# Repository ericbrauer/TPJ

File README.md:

# TPJ
Final Project for ECT @ Seneca. "Project Skylight"

# PROJECT SKYLIGHT
Eric Brauer 

## Executive Summary
Project Skylight is an Internet-connected light that simulates daylight cycles. It’s meant for
use in places where there are no external windows, and it can be used to get a quick visual
reference for the time of day. Project skylight is composed of a small microcontroller with wifi
capabilities, and 16 RGB LEDs. The device is meant to run with very little set-up, but a
web-based user interface can be used for further configuration. In the report, the operation
and specifications of Project Skylight are covered in more detail.

## Functional Features
The product requirements, as envisioned, are as follows:
- Project Skylight (PS) asks for WiFi credentials, and connects to a WiFi router.
- PS serves a webpage which is used to configure the device and to provide the user’s
city of residence.
- PS uses the OpenWeatherMap API to get the time of dawn and dusk. The device
also uses an NTP server to synchronise the current time.
- PS changes the colour and brightness of LEDs based on current time in reference to
sunrise and sunset times.
- PS monitors a potentiometer, which will be used to dim or turn off the LED light.
- Further configuration is possible from the web interface. This includes setting manual
daylight times.

## Product Specifications
- Powered from micro USB port
- Operates at nominal indoor temperatures, not for outdoor use
- Luminosity of around 200 - 400 Lumens
- WiFi range 20m
- Current consumption no higher than 1.5A

## Theory of Operation
### Power Concerns
The ESP-12f requires a typical voltage of 3.3 Volts. The Neopixel array require a voltage of 4
to 7 Volts. Thus a voltage regulation stage is required. USB provides 5 Volts, and this power
is used for the Neopixels. Power for the ESP-12f is supplied by an LD1117.

Power consumption is based heavily on several factors: transmission and reception by the
WiFi module on the ESP-12f, signal strength of the same, and brightness levels of the
Neopixels. If a single Neopixel is set to white with maximum brightness, then each of its
three RGB LEDs requires 20 mA. There is never a situation when the Skylight is generating
this state, however. Full brightness of the daytime SkyState would represent the maximum
current consumption.

4 LEDs displaying white = 60mA * 4 240mA

12 LEDs displaying cyan = 40mA * 12 480mA

Total Current for Neopixels: **720mA**

In addition, the ESP-12f requires a maximum of 100mA. Meaning that a USB adapter rated
at 1A should be sufficient for proper function and also provide a buffer of almost 20%.

### Initial State / Connectivity
The ESP-12f is a popular IC among the maker community, and much work has been done to
implement a thorough Arduino library which exposes much of the connectivity capability of
the chip. The Skylight in particular makes use of several libraries to implement the initial
Access Point state (used to enter WiFi credentials), to communicate to OpenWeatherMap,
and to serve a web-based user interface.

**ESP8266WiFi** exposes functions for connecting to a WiFi access point and communicating
over TCP/IP.

**ESP8266WebServer** allows to ESP to also act as a web server, and serve HTTP code to
clients.

**ESP8266mDNS** provides a ‘micro DNS’ server which will associate a URL with whatever IP
address is assigned to the ESP’s web server.

**WifiManager** checks flash for a WiFi SSID and password that was previously used to
connect. If these don’t exist, WifiManager will set the ESP-12 to station mode with an SSID
set in software. The user can connect to this access point, and then navigate to the url
specified by the micro-DNS server. From this webpage, the user has the option to scan for
available access points, and then enter a password to connect to this access point. From
this point, the ESP exits station mode and attempts to connect to the access point as a
client. If it is successful, these credentials will be saved in flash memory to be used on
startup.

### The Web Interface
The ESP handles web requests directed at the url created by the micro DNS server. On the
Skylight, the url is skylight.local. The main interface is located at the root. Other webpages
are used to acknowledge user requests, and exist at /submit, /demo and /reset. All other
requests will result in a HTTP code of 404.
A typical user request is to manually change the time at which a sunset event occurs. The
time desired is typed into text boxes, and the ‘save’ button is pressed. Information inside the
text boxes is saved as arguments. The arguments are validated first. The arguments are
checked to ensure that they are numerical and in a proper 12-hour time format. A bad
request will result in a ‘bad request’ message and a link back to the root page. A good
request will be accepted. Finally, the browser will navigate to skylight.local/submit, where the
user is notified that the alarm has been set.

### Adafruit NeoPixel Array
Neopixels are addressable RGB LEDs. Control circuitry, LEDs, and internal oscillators are all
included in one package. Data can be received from a microcontroller at speeds of 800kbps,
and outputted to the next neopixel. This allows an array of neopixels to be controlled from
one data pin.
Each neopixel requires 24bits of information. The first neopixel uses 24 bits to set the values
of discrete red, green and blue LEDs. Each of these LEDs takes a PWM 8-bit signal to set its
intensity, resulting in 255 possible states. Once the state of neopixel has been set,
subsequent data is amplified and sent through a ‘Data Out’ line to program the next
neopixel. The advantage of neopixels is their flexibility, but larger arrays will require far more
memory and processing than some microcontrollers can provide. Since the Skylight uses
only 16 neopixels, performance requirements are relatively light.9
Adafruit provides an Arduino Library for communicating with the Neopixel array. The
Neopixels are powered from a 5V VCC line and the data line is connected to the ESP’s
GPIO pin 14.
### Brightness Control
A potentiometer is connected to the ESP-12’s single Analog-to-Digital converter. A standard
Arduino library function is used to convert this number to a 10-bit value, which is then to an
8-bit value using bit shift. The 8-bit value is used as an argument for the setBrightness
function which is part of the Adafruit Neopixel library. Using the ADC with interrupts proved
to be problematic, and so the ADC is polled in loop() and if its value changes, the
setBrightness function is called. The potentiometer is connected to the ADC pin identified as
0.
### Setting dusk_time and dawn_time From OpenWeatherMap.org
OpenWeatherMap provides an API that can be used for free with registration for a smaller
number of requests. For the Skylight prototype, this is sufficient. Documentation for the API
is located at ​ [OpenWeatherMap](http://openweathermap.org/current).​ The API can be used with several different
formats of location data; for simplicity’s sake a GET request is used encoded with the city
and country code are used along with an API key.
The HTTP response is in a JSON format. First, the HTTP header of the response is
discarded. Then ArduinoJson library is used to parse the response. Most information is
related to weather conditions and is not used. The sunrise and sunset times are sent in
epoch time based on UTC. In order to set this to local time, a timezone offset is added to
these times and the result is stored in memory.
### Using NTP to Sync Local Time
NTPClient is another library used to communicate with NTP servers. This is used with
TimeLib to set the ESP’s time. A timezone offset is required by the library.
### State Machine
Assuming that NTP and GET Requests have succeeded, the Skylight will compare current
time with the next scheduled event. Once current time is within forty minutes of a sunrise or
sunset, the Skylight enters a DUSK or DAWN event. Both events are identical, but DUSK
occurs in reverse order.
There are three parts to a transition, and each takes 20 minutes. Two of the parts of the
transition occur before the event time, and one occurs after. Each part of the transition is
handled by a function, and each function takes as an argument an 8-bit number.

`SkyState1(0-255) SkyState2(0-255) SkyState3(0-255)`

Duration: 1200 seconds Duration: 1200 seconds Duration: 1200 seconds
In the case of DAWN, the actual sunrise_time is the time between SkyState2 and SkyState3.
In order to set the argument for each SkyState function, a simple equation derived from the
Radiometric Equation is used.

`y = (x - 2400) / (-3600 / 765)`

Where x is equal to seconds until event and y is equal to the skyState argument.
What this means is that approximately every 7 seconds, SkyState functions will increment
the levels of the Neopixel LEDs which results in a simulated dawn or dusk event. Once the
current time is over twenty minutes past the last event, the state machine will return to a
state where it decides if it is waiting for dawn or waiting for dusk. If both dawn and dusk
events are earlier than the current time, the state machine will attempt to request new times
from OpenWeatherMap.

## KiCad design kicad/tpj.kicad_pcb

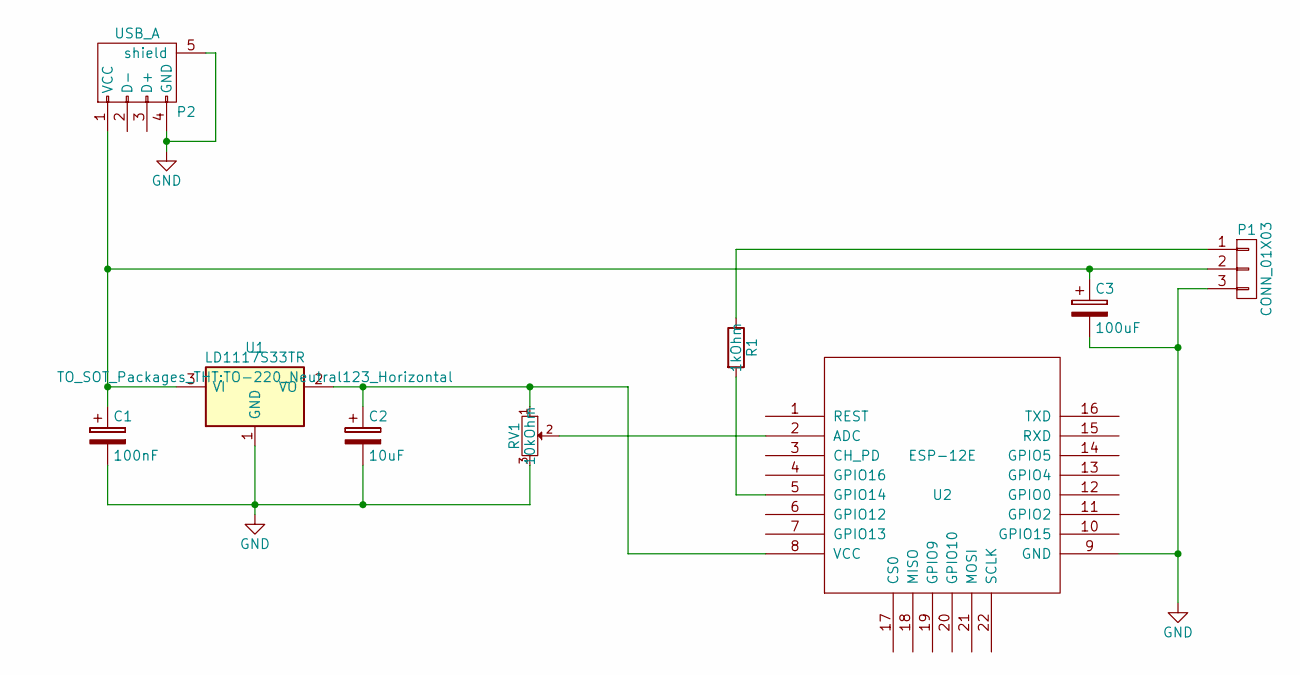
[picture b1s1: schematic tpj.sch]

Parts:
C1: 100nF; C_Axial_D5_L11_P18
C2: 10uF; C_Axial_D5_L11_P18
C3: 100uF; C_Axial_D5_L11_P18
P1: CONN_01X03; Pin_Header_Angled_1x03
P2: USB_A; USB_Micro-B
R1: 1kOhm; Resistor_Horizontal_RM7mm
RV1: 10kOhm; Potentiometer_WirePads_largePads
U1: LD1117S33TR; TO-220_Neutral123_Horizontal
U2: ESP-12E

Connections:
GND: C1.2, C2.2, C3.2, P1.3, P2.4 (GND), P2.5 (shield), RV1.3, U1.1 (GND), U2.9 (GND)
unnamed: C1.1, C3.1, P1.2, P2.1 (VCC), U1.3 (VI)
unnamed: C2.1, RV1.1, U1.2 (VO), U2.8 (VCC)
unnamed: P1.1, R1.1
unnamed: R1.2, U2.5 (GPIO14)
unnamed: RV1.2, U2.2 (ADC)

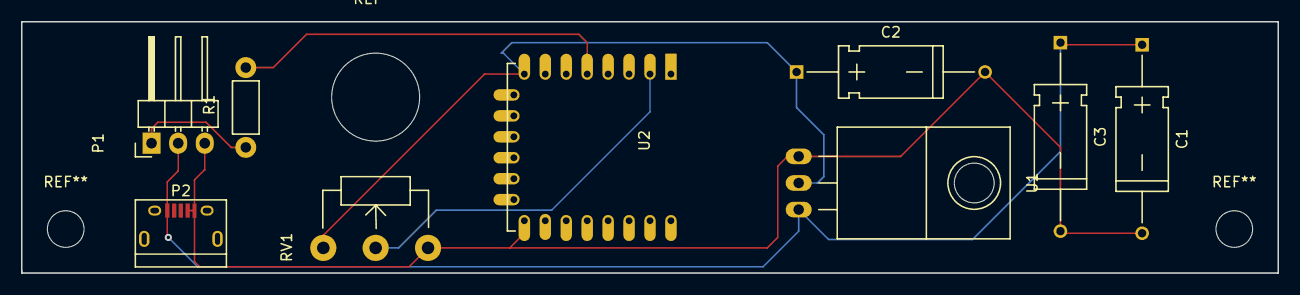
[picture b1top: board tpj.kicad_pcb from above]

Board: 2 copper layers, 120.0 x 24.0 mm, 9 parts (0 on the bottom side), 6 nets.

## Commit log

2017-01-22 added NTP capability
2017-02-01 added a get request function
2017-02-02 add function arguments, json parsing
2017-02-02 some fixes, parsing needs escaped quotes??
2017-02-02 need to remove the header.
2017-02-05 added neopixel library
2017-02-05 added code for neopixel.
2017-02-15 fixed json parsing issue
2017-02-19 cleaned up formatting, chose lat/long, different formatting
2017-02-19 using time lib
2017-02-20 change to json trimming
2017-03-05 added kicad files
2017-03-06 some functions for daylight, and new api
2017-03-06 added the alarm library. But maybe don't need it?
2017-03-14 implemented web server, and connection manager. more TODO
2017-03-17 added schematic
2017-03-19 added complete gui to webpage
2017-03-19 added a submit handler
2017-03-19 see the submit arguments
2017-03-19 fixes to server handling of post arguments
2017-03-19 started handling of arguments
2017-03-19 fixes to response handling so far
2017-03-19 corrected for daylight savings time
2017-03-21 some more dicking around
2017-03-21 two more skytransitions
2017-03-22 moved things into new libraries
2017-03-22 adding missing libraries
2017-03-22 refactoring continues
2017-03-22 got closer, but think gonna abandon this
2017-03-22 reverting class/object scheme. Still issue with server not living in scope
2017-03-25 leaving refactor for now.
2017-03-25 implementing state machine in main
2017-03-26 troubleshooting in progress.
2017-03-28 further revisions
2017-04-01 dawn_time and dusk_time add timezone offset
2017-04-01 parse sunrise and sunset will set dusk and dawn_time
2017-04-03 fixed the manual alarms
2017-04-03 some cleanup of code
2017-04-04 initial commit with comments
2017-04-04 fixed merge conflict. adding comments
2017-04-04 commented code up to setup()
2017-04-04 finished comments and cleanup
2017-04-04 including assets folder with presentation, documents, datasheets, schematic
2017-04-05 added final report. Done
2018-01-24 Updated Readme.
    Readme now describes the project in more detail, quoted from the (final report)[assets/FinalReport.pdf]
